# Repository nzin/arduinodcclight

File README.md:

View this project on [CADLAB.io](https://cadlab.io/node/818). 

A versatile Arduino stationary dcc decoder
==========================================

When constructing my dcc based train model, I looked for dcc decoder to pilot light (SMD 0402, or standard led), but had difficulty to program them for custom scenario (blinking, road works style, …). There are also some DIY dcc decoder (opendcc decoder) but didn’t manage to make them working. So I decided to create my own stationary dcc decoder based on Arduino (nano), to be able to reprogram it at wish.

This decoder is pretty simple, you can
 * assign it a dcc address (via a learning switch button)
 * connect LED lights, or a relay
 * choose the light mode if you connected lights. There are 3 different modes you can choose via a push button: constant light (on or off), flicker mode, or 3 way road work lights mode

It has been designed to be powered by a 16V AC, but can be as well be powered via DCC signal (15v or 18v), or a DC signal.

Using it
========

Powering
--------
This decoder is designed to be powered by a 16V AC power source. It is possible to power it with the dcc signal, but my circuit is not the most power efficient stationary decoder (due to the fact that it power lights, an arduino and eventually a relay), so you don’t want that, except in rare situation.

This is why there are 2 set of cables:
 * one for the 16V AC
 * one for the DCC signal

Assign a dcc address
--------------------

To assign a dcc address, you have to use the learning switch opposite to the Arduino.
In that position, each time it see a stationary decoder command coming on, it will store it as its new address (and will acknowledge that by blinking the status led).
So to assign a dcc address you just have to
 * push the learning switch opposite to the Arduino.
 * send a command with the wished address
 * you will see the status led blinking, stating that it saw the address and learned it
 * push back the learning switch towards the Arduino

Connect light
-------------

On the bottom of the card, you have 3 slots for leds. The + of the led must be on the left. Normaly you can connect only one led per slot (due to the nominal tension that each led has, 2 different led don't have the exact same nominal tension).

If you use the push button, you will circle between 3 modes:
 * constantly on (or off)
 * flickering seldomly
 * 3 way road work lights (it will switch on the first light, then the second light, then the 3rd light, and cycle again to the first light)

You just has to use the push button to cycle between the 3 modes. The little status led, will tell you in which mode you are.

Connect relay
-------------

Close to the lights there is a block of 3 pins for the relay (if you decide to build it), which are in this order: low ouput, input, high output.
So the one on the middle is your input (whatever your input is), and the relay will connect it either to the left pin or to the right pin.

Connect to the other IO
=======================

There are some generic IO available, that expose
 * 5v and ground
 * analog pins 6 and 7
 * and digital pins 6 and 7

You can use them at your own advantage, but you will need to reprogram the Arduino to you own purpose: I didn’t program anything on them.

Assemble it
===========

If you don’t want to assemble, or just want the PCB already fabricated, contact me, and I can provide it for you: nicolas.zin@gmail.com

If you prefer to fully assemble it, you will need to get the PCB, and of course the components.
The PCB gerber files are here: https://github.com/nzin/arduinodcc/blob/master/arduinov1.2.zip (for the eagle source check below)

To fully assemble it, the full Bill Of Material is:

item                    |how many |ref
------------------------|---------|------------------------------------
arduino nano            |1        |aliexpress
bridge rectifier        |1        |mouser 625-B40C800G-E4
DC-DC converter (9VDC)  |1        |mouser 490-V7809-1000 (or cheaper : voltage regulator mouser 511-L7809CV in that case buy also a heatsink)
capa 330uF              |1        |mouser 667-EEU-FM1C331
capa 10uF               |1        |mouser 581-TAP106K025SCS
R 10k ohm               |4        |mouser 71-CCF50-10K
R 1k ohm                |1        |mouser 603-CFR-12JR-521K
diode 4148              |1        |mouser 512-1N4148
toggle button           |1        |sparkfun COM-00102 (maybe mouser 633-SS12SDP2)
push button             |1        |SPARKUN COM-00097 (ou mouser 693-1301.9308)
led                     |1        |mouser 941-C4SMFRJSCT0W0BB2 (or 630-HLMP-1301)
terminal block  2 pos   |10       |mouser 651-1729128
headers                 |2        |mouser 855-M20-7821546
high speed optocoupler  |1        |mouser 630-6N137
R 200 ohm               |9        |mouser 71-CCF50-200
shottky diode           |1        |mouser 833-SR108-TP

Reprogram it
============

If you are familiar with Arduino programming, you can re-program it to whatever needs you have. That the beauty of it. Here are the arduino sources: https://github.com/nzin/arduinodcc/blob/master/arduinoSource/dccduino.ino

It is based on the dcc decoder library from Minabay you will need to install: https://github.com/MynaBay/DCC_Decoder

Extend it
=========

If you want to develop your own dcc decoder, I provide you the eagle source: https://github.com/nzin/arduinodcc/blob/master/arduinoDcc1.2.sch and https://github.com/nzin/arduinodcc/blob/master/arduinoDcc1.2.brd

Feel free to adapt it to your needs, but I provide it as is, i.e. I can answer some question but if you decide to change the layout, you are on your own

Licence
=======
The Arduino code and the Eagle schema are under the [GPL v2](https://github.com/nzin/arduinodcc/blob/master/gpl-2.0.txt)

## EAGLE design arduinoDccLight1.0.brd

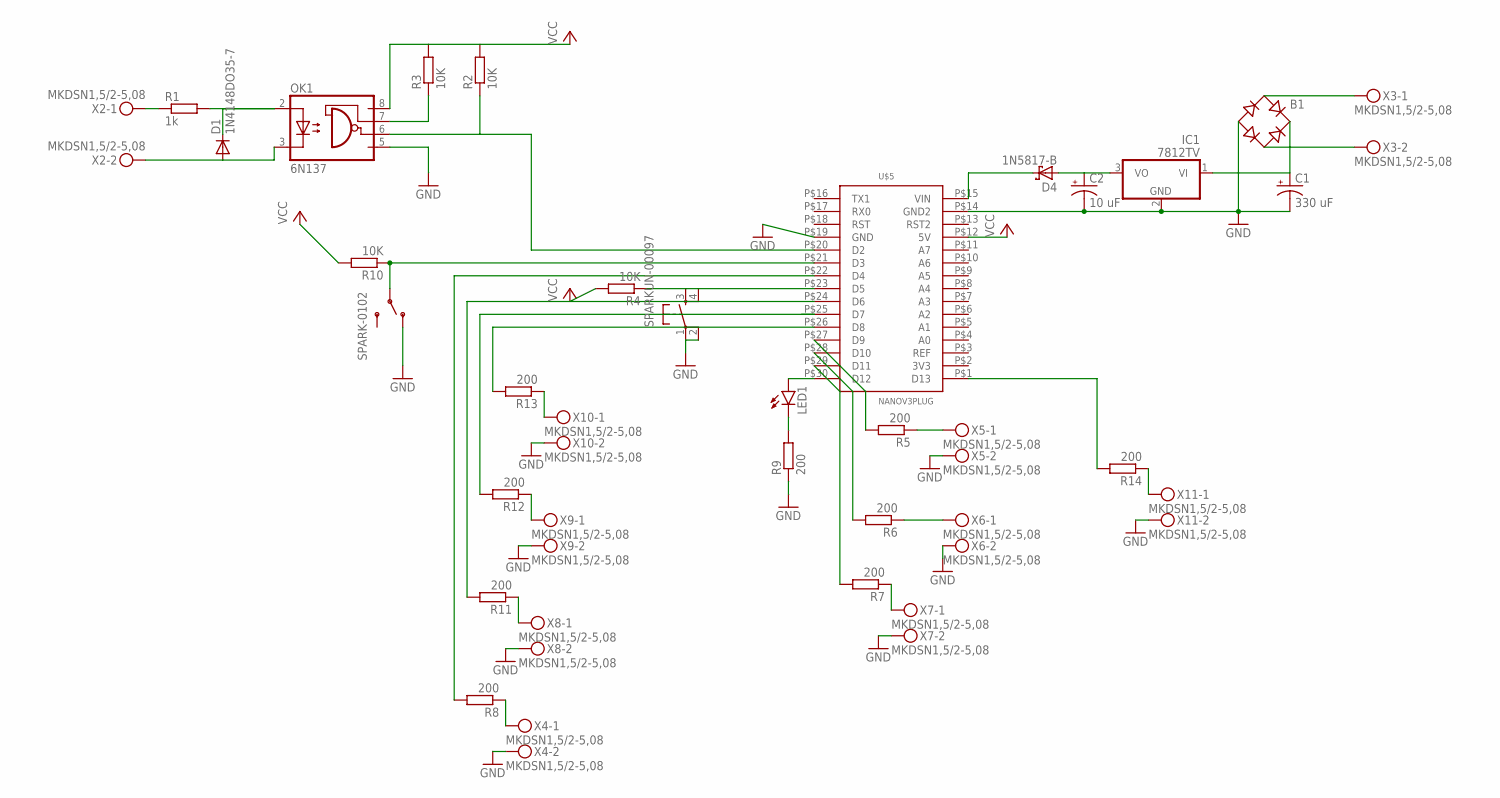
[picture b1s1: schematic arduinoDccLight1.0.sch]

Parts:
B1: RB1A
C1: 330 uF; CPOL-RADIAL-100UF-25V
C2: 10 uF; CPOL-RADIAL-100UF-25V
D1: 1N4148DO35-7; DO35-7
D4: 1N5817-B; DO41-7.6
IC1: 7812TV; TO220V
LED1: LED3MM
OK1: 6N137; DIL08
R1: 1k; 0207/10
R2, R3, R4, R10: 10K; 0207/10
R5, R6, R7, R8, R11, R12, R13, R14: 200; 0207/10
R9: 200; 0204/7
SPARK-0102: SWITCH-SPDTPTH; SWITCH-SPDT
SPARKUN-00097: TAC_SWITCHPTH; TACTILE-PTH
U$5: NANOV3PLUG; HEADER15-2
X2, X3, X4, X5, X6, X7, X8, X9, X10, X11: MKDSN1,5/2-5,08

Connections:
GND: B1.-, C1.2 (-), C2.2 (-), IC1.2 (GND), OK1.5 (GND), R9.1, SPARK-0102.1 (O), SPARKUN-00097.1, SPARKUN-00097.2, U$5.P$14 (GND2), U$5.P$19 (GND), X4.2, X5.2, X6.2, X7.2, X8.2, X9.2, X10.2, X11.2
unnamed: R1.1, X2.1
unnamed: D1.C, OK1.2 (A), R1.2
unnamed: D1.A, OK1.3 (C), X2.2
unnamed: R10.1, SPARK-0102.2, U$5.P$21 (D3)
unnamed: R8.1, X4.1
unnamed: OK1.6 (VO), R2.1, U$5.P$20 (D2)
unnamed: OK1.7 (VE), R3.1
unnamed: B1.AC1, X3.1
unnamed: R8.2, U$5.P$22 (D4)
unnamed: R11.1, X8.1
unnamed: R11.2, U$5.P$24 (D6)
unnamed: R12.1, X9.1
unnamed: R6.1, X6.1
unnamed: R7.2, U$5.P$29 (D11)
unnamed: R6.2, U$5.P$28 (D10)
unnamed: R5.2, U$5.P$27 (D9)
unnamed: R5.1, X5.1
unnamed: R4.1, SPARKUN-00097.3, SPARKUN-00097.4, U$5.P$23 (D5)
unnamed: R12.2, U$5.P$25 (D7)
unnamed: R13.1, X10.1
unnamed: R13.2, U$5.P$26 (D8)
unnamed: B1.AC2, X3.2
unnamed: B1.+, C1.1 (+), IC1.1 (VI)
unnamed: LED1.K (C), R9.2
unnamed: LED1.A, U$5.P$30 (D12)
unnamed: R7.1, X7.1
unnamed: C2.1 (+), D4.A, IC1.3 (VO)
unnamed: R14.1, X11.1
unnamed: R14.2, U$5.P$1 (D13)
unnamed: D4.C, U$5.P$15 (VIN)
VCC: OK1.8 (VCC), R2.2, R3.2, R4.2, R10.2, U$5.P$12 (5V)

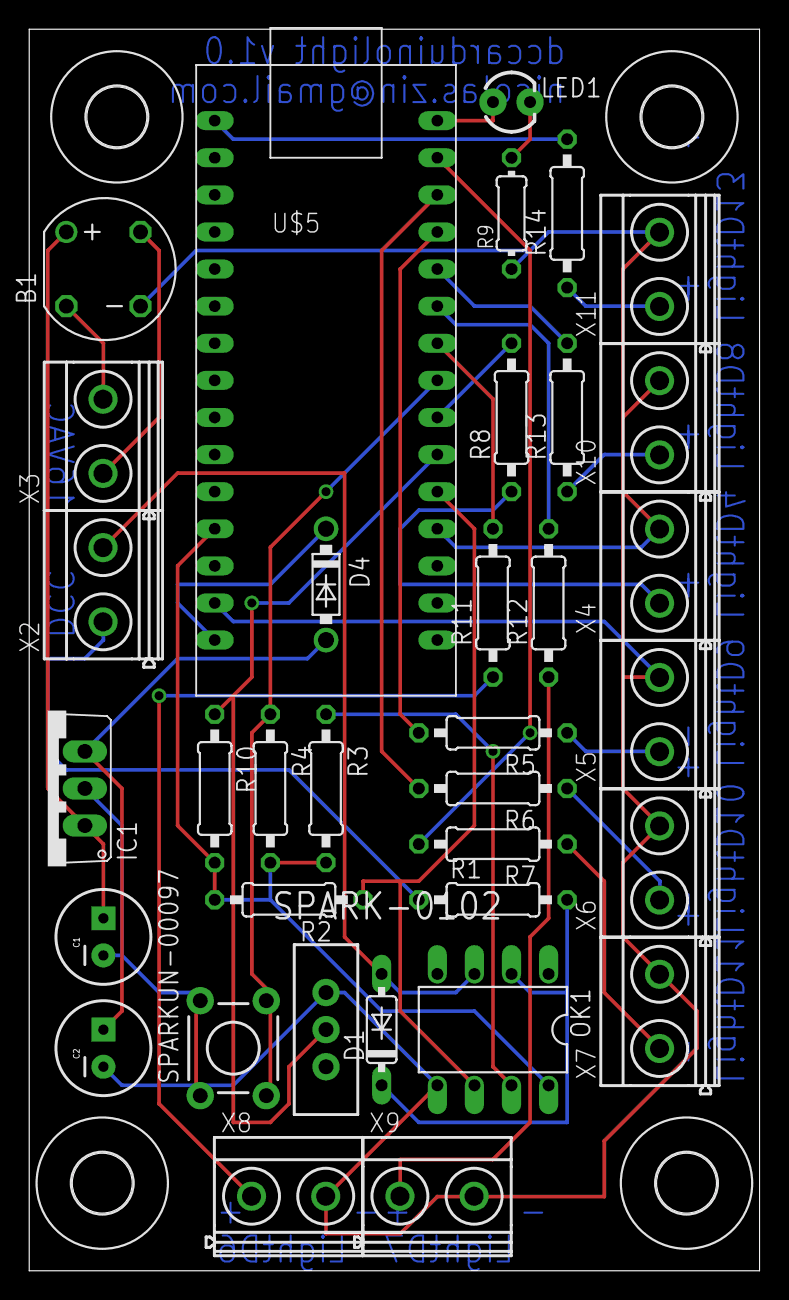
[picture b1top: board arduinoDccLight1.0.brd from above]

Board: 2 copper layers, 50.0 x 85.0 mm, 39 parts (0 on the bottom side), 32 nets.

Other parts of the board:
U$1, U$2, U$3, U$4: 4,1

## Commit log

2017-01-06 update BOM
2017-01-06 shottky diode
2017-01-11 not tested yet
2017-01-11 remove relay related code, and fix a bug
2017-01-11 bugfix
2017-01-11 put the light in the PCB order
2017-02-08 refresh BOM
2018-04-02 Backlink to CADLAB.io has been added.

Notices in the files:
parts and their libraries:
SparkFun-Electromechanical: Licensing: Creative Commons ShareAlike 4.0 International - https://creativecommons.org/licenses/by-sa/4.0
